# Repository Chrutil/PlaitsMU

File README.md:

# PlaitsMU
The Plaits Macro Oscillator ported to MU

This project is the Plaits Macro Oscillator by Mutable Instruments ported to MU large format modular.

The size of the PCB has been increased and the layout expanded for a 2MU module.
The footprint of most components have been changed to a larger 0805 size, for an easier build.
A few components were left at 0603 size where I could not find a suitable replacement.
The Power connector is a Synthesizers.com standard using -15v/+15v.
There are 12v power regulators added to feed the module the +/-12v it expects.
There is also a footprint for a MOTM power connector, but it is untested. 
I also suspect the io PCB is too wide for a double wide MOTM panel, but I have only tested MU so you are on your own there.

The best way is to select components is to look at the original BOM and pick the appropriate components with the expanded footprint.
I added a file with my parts selection, with no guarantees that I got it correct.

The STM32 mcu is the same as the original module and a very fine pitched IC with 0.5mm pitch so that will be the most challenging part.
I suggest starting with that one to make sure you got that right before populating the rest of the board.

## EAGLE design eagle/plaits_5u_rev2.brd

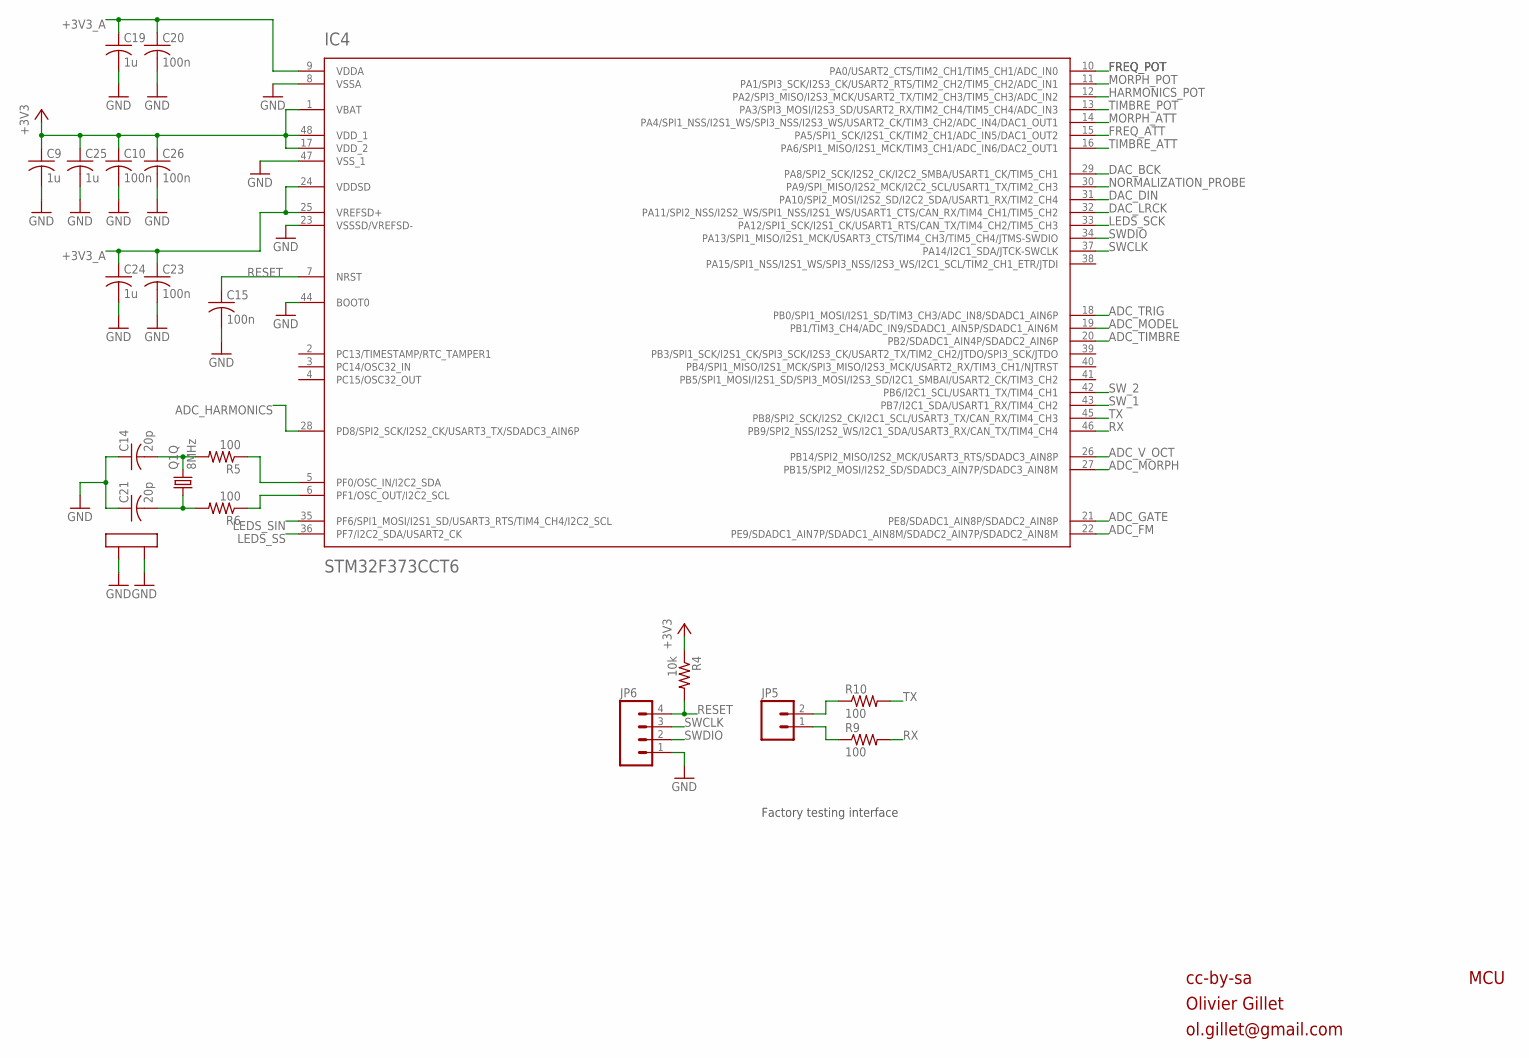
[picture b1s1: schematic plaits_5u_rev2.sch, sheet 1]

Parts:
C9, C19, C24, C25: 1u; C0805
C10, C15, C20, C23, C26: 100n; C0805
C14, C21: 20p; C0805
IC4: STM32F373CCT6; LQFP48
JP5: M02PTH; 1X02
JP6: M04PTH; 1X04
Q1: 8MHz; CTS406
R4: 10k; R0805
R5, R6, R9, R10: 100; R0805

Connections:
+3V3: C9.1, C10.1, C25.1, C26.1, IC4.1 (VBAT), IC4.17 (VDD_2), IC4.48 (VDD_1), R4.1; also elsewhere on the board
+3V3_A: C19.1, C20.1, C23.1, C24.1, IC4.9 (VDDA), IC4.24 (VDDSD), IC4.25 (VREFSD+); also elsewhere on the board
ADC_FM: IC4.22 (PE9/SDADC1_AIN7P/SDADC1_AIN8M/SDADC2_AI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); also elsewhere on the board
ADC_GATE: IC4.21 (PE8/SDADC1_AIN8P/SDADC2_AIN8P); also elsewhere on the board
ADC_HARMONICS: IC4.28 (PD8/SPI2_SCK/I2S2_CK/USART3_TX/SDADC3_A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); also elsewhere on the board
ADC_MODEL: IC4.19 (PB1/TIM3_CH4/ADC_IN9/SDADC1_AIN5P/SDADC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); also elsewhere on the board
ADC_MORPH: IC4.27 (PB15/SPI2_MOSI/I2S2_SD/SDADC3_AIN7P/SDA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); also elsewhere on the board
ADC_TIMBRE: IC4.20 (PB2/SDADC1_AIN4P/SDADC2_AIN6P); also elsewhere on the board
ADC_TRIG: IC4.18 (PB0/SPI1_MOSI/I2S1_SD/TIM3_CH3/ADC_IN8/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); also elsewhere on the board
ADC_V_OCT: IC4.26 (PB14/SPI2_MISO/I2S2_MCK/USART3_RTS/SDAD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); also elsewhere on the board
DAC_BCK: IC4.29 (PA8/SPI2_SCK/I2S2_CK/I2C2_SMBA/USART1_C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); also elsewhere on the board
DAC_DIN: IC4.31 (PA10/SPI2_MOSI/I2S2_SD/I2C2_SDA/USART1_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); also elsewhere on the board
DAC_LRCK: IC4.32 (PA11/SPI2_NSS/I2S2_WS/SPI1_NSS/I2S1_WS/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); also elsewhere on the board
FREQ_ATT: IC4.15 (PA5/SPI1_SCK/I2S1_CK/TIM2_CH1/ADC_IN5/D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); also elsewhere on the board
FREQ_POT: IC4.10 (PA0/USART2_CTS/TIM2_CH1/TIM5_CH1/ADC_IN0); also elsewhere on the board
GND: C9.2, C10.2, C14.1, C15.2, C19.2, C20.2, C21.1, C23.2, C24.2, C25.2, C26.2, IC4.8 (VSSA), IC4.23 (VSSSD/VREFSD-), IC4.44 (BOOT0), IC4.47 (VSS_1), JP6.1, Q1.2 (LID1), Q1.4 (LID2); also elsewhere on the board
HARMONICS_POT: IC4.12 (PA2/SPI3_MISO/I2S3_MCK/USART2_TX/TIM2_C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); also elsewhere on the board
LEDS_SCK: IC4.33 (PA12/SPI1_SCK/I2S1_CK/USART1_RTS/CAN_TX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); also elsewhere on the board
LEDS_SIN: IC4.35 (PF6/SPI1_MOSI/I2S1_SD/USART3_RTS/TIM4_C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); also elsewhere on the board
LEDS_SS: IC4.36 (PF7/I2C2_SDA/USART2_CK); also elsewhere on the board
MORPH_ATT: IC4.14 (PA4/SPI1_NSS/I2S1_WS/SPI3_NSS/I2S3_WS/U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); also elsewhere on the board
MORPH_POT: IC4.11 (PA1/SPI3_SCK/I2S3_CK/USART2_RTS/TIM2_CH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); also elsewhere on the board
unnamed: IC4.5 (PF0/OSC_IN/I2C2_SDA), R5.1
unnamed: IC4.6 (PF1/OSC_OUT/I2C2_SCL), R6.1
unnamed: C14.2, Q1.3 (2), R5.2
unnamed: JP5.2, R10.1
unnamed: C21.2, Q1.1, R6.2
unnamed: JP5.1, R9.1
NORMALIZATION_PROBE: IC4.30 (PA9/SPI_MISO/I2S2_MCK/I2C2_SCL/USART1_T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); also elsewhere on the board
RESET: C15.1, IC4.7 (NRST), JP6.4, R4.2
RX: IC4.46 (PB9/SPI2_NSS/I2S2_WS/I2C1_SDA/USART3_RX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), R9.2
SWCLK: IC4.37 (PA14/I2C1_SDA/JTCK-SWCLK), JP6.3
SWDIO: IC4.34 (PA13/SPI1_MISO/I2S1_MCK/USART3_CTS/TIM4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), JP6.2
SW_1: IC4.43 (PB7/I2C1_SDA/USART1_RX/TIM4_CH2); also elsewhere on the board
SW_2: IC4.42 (PB6/I2C1_SCL/USART1_TX/TIM4_CH1); also elsewhere on the board
TIMBRE_ATT: IC4.16 (PA6/SPI1_MISO/I2S1_MCK/TIM3_CH1/ADC_IN6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); also elsewhere on the board
TIMBRE_POT: IC4.13 (PA3/SPI3_MOSI/I2S3_SD/USART2_RX/TIM2_CH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); also elsewhere on the board
TX: IC4.45 (PB8/SPI2_SCK/I2S2_CK/I2C1_SCL/USART3_TX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), R10.2

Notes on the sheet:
cc-by-sa
Olivier Gillet
ol.gillet@gmail.com
MCU
Factory testing interface

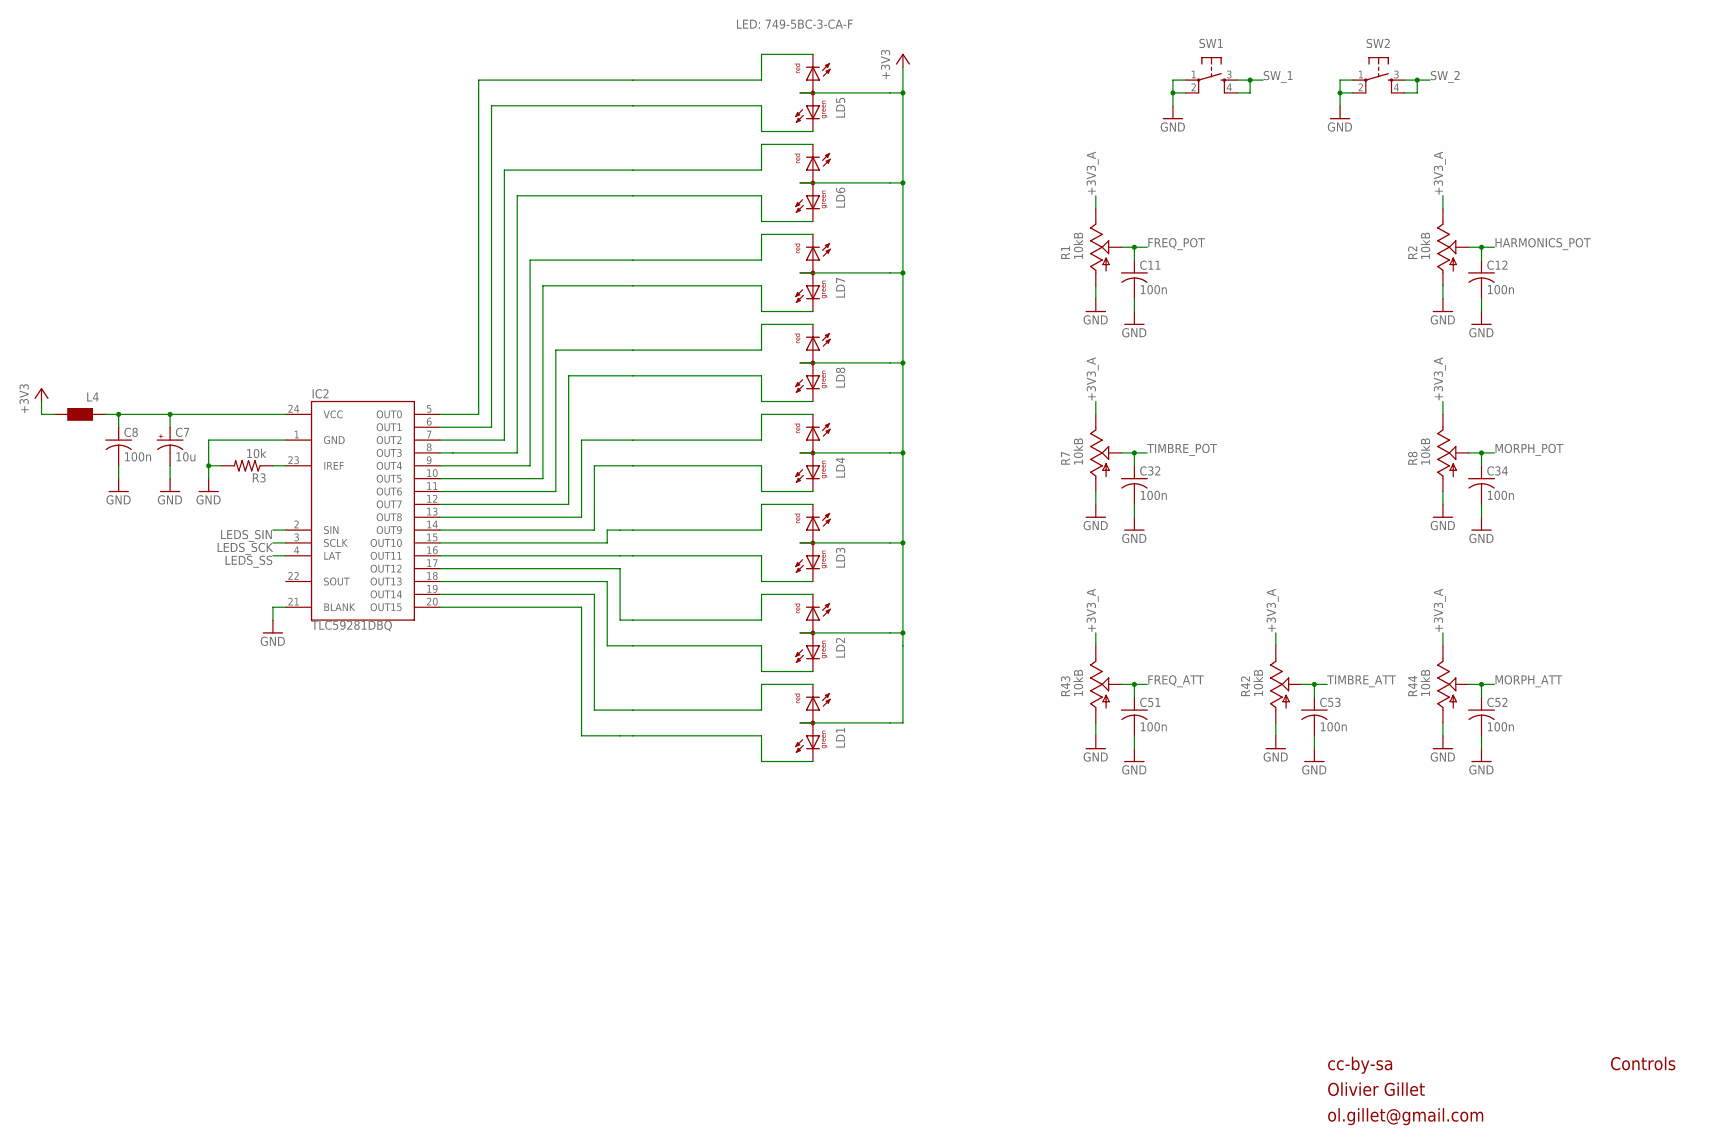
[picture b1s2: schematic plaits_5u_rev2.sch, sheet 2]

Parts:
C7: 10u; PANASONIC_A
C8, C11, C12, C32, C34, C51, C52, C53: 100n; C0805
IC2: TLC59281DBQ; TSSOP24_0635
L4: WE-CBF_0805; 0805
LD1, LD2, LD3, LD4, LD5, LD6, LD7, LD8: DUOLED-RG-A; DUOLED-A-5MM
R1, R2, R7, R8: 10kB; ALPS_POT_VERTICAL_PS
R3: 10k; R0805
R42, R43, R44: 10kB; ALPS_POT_VERTICAL
SW1, SW2: TAC_SWITCHPTH; TACTILE-PTH

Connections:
+3V3: L4.2, LD1.A, LD2.A, LD3.A, LD4.A, LD5.A, LD6.A, LD7.A, LD8.A; also elsewhere on the board
+3V3_A: R1.P$1 (E), R2.P$1 (E), R7.P$1 (E), R8.P$1 (E), R42.P$1 (E), R43.P$1 (E), R44.P$1 (E); also elsewhere on the board
FREQ_ATT: C51.1, R43.P$2 (S); also elsewhere on the board
FREQ_POT: C11.1, R1.P$2 (S); also elsewhere on the board
GND: C7.-, C8.2, C11.2, C12.2, C32.2, C34.2, C51.2, C52.2, C53.2, IC2.1 (GND), IC2.21 (BLANK), R1.P$3 (A), R2.P$3 (A), R3.2, R7.P$3 (A), R8.P$3 (A), R42.P$3 (A), R43.P$3 (A), R44.P$3 (A), SW1.1, SW1.2, SW2.1, SW2.2; also elsewhere on the board
HARMONICS_POT: C12.1, R2.P$2 (S); also elsewhere on the board
LEDS_SCK: IC2.3 (SCLK); also elsewhere on the board
LEDS_SIN: IC2.2 (SIN); also elsewhere on the board
LEDS_SS: IC2.4 (LAT); also elsewhere on the board
MORPH_ATT: C52.1, R44.P$2 (S); also elsewhere on the board
MORPH_POT: C34.1, R8.P$2 (S); also elsewhere on the board
unnamed: IC2.12 (OUT7), LD8.CX (CG)
unnamed: IC2.11 (OUT6), LD8.CR
unnamed: IC2.10 (OUT5), LD7.CX (CG)
unnamed: IC2.9 (OUT4), LD7.CR
unnamed: IC2.8 (OUT3), LD6.CX (CG)
unnamed: IC2.13 (OUT8), LD4.CR
unnamed: IC2.7 (OUT2), LD6.CR
unnamed: IC2.14 (OUT9), LD4.CX (CG)
unnamed: IC2.6 (OUT1), LD5.CX (CG)
unnamed: IC2.15 (OUT10), LD3.CR
unnamed: IC2.16 (OUT11), LD3.CX (CG)
unnamed: IC2.17 (OUT12), LD2.CR
unnamed: IC2.18 (OUT13), LD2.CX (CG)
unnamed: IC2.19 (OUT14), LD1.CR
unnamed: IC2.5 (OUT0), LD5.CR
unnamed: IC2.20 (OUT15), LD1.CX (CG)
unnamed: C7.+, C8.1, IC2.24 (VCC), L4.1
unnamed: IC2.23 (IREF), R3.1
SW_1: SW1.3, SW1.4; also elsewhere on the board
SW_2: SW2.3, SW2.4; also elsewhere on the board
TIMBRE_ATT: C53.1, R42.P$2 (S); also elsewhere on the board
TIMBRE_POT: C32.1, R7.P$2 (S); also elsewhere on the board

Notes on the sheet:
cc-by-sa
Olivier Gillet
ol.gillet@gmail.com
Controls
LED: 749-5BC-3-CA-F

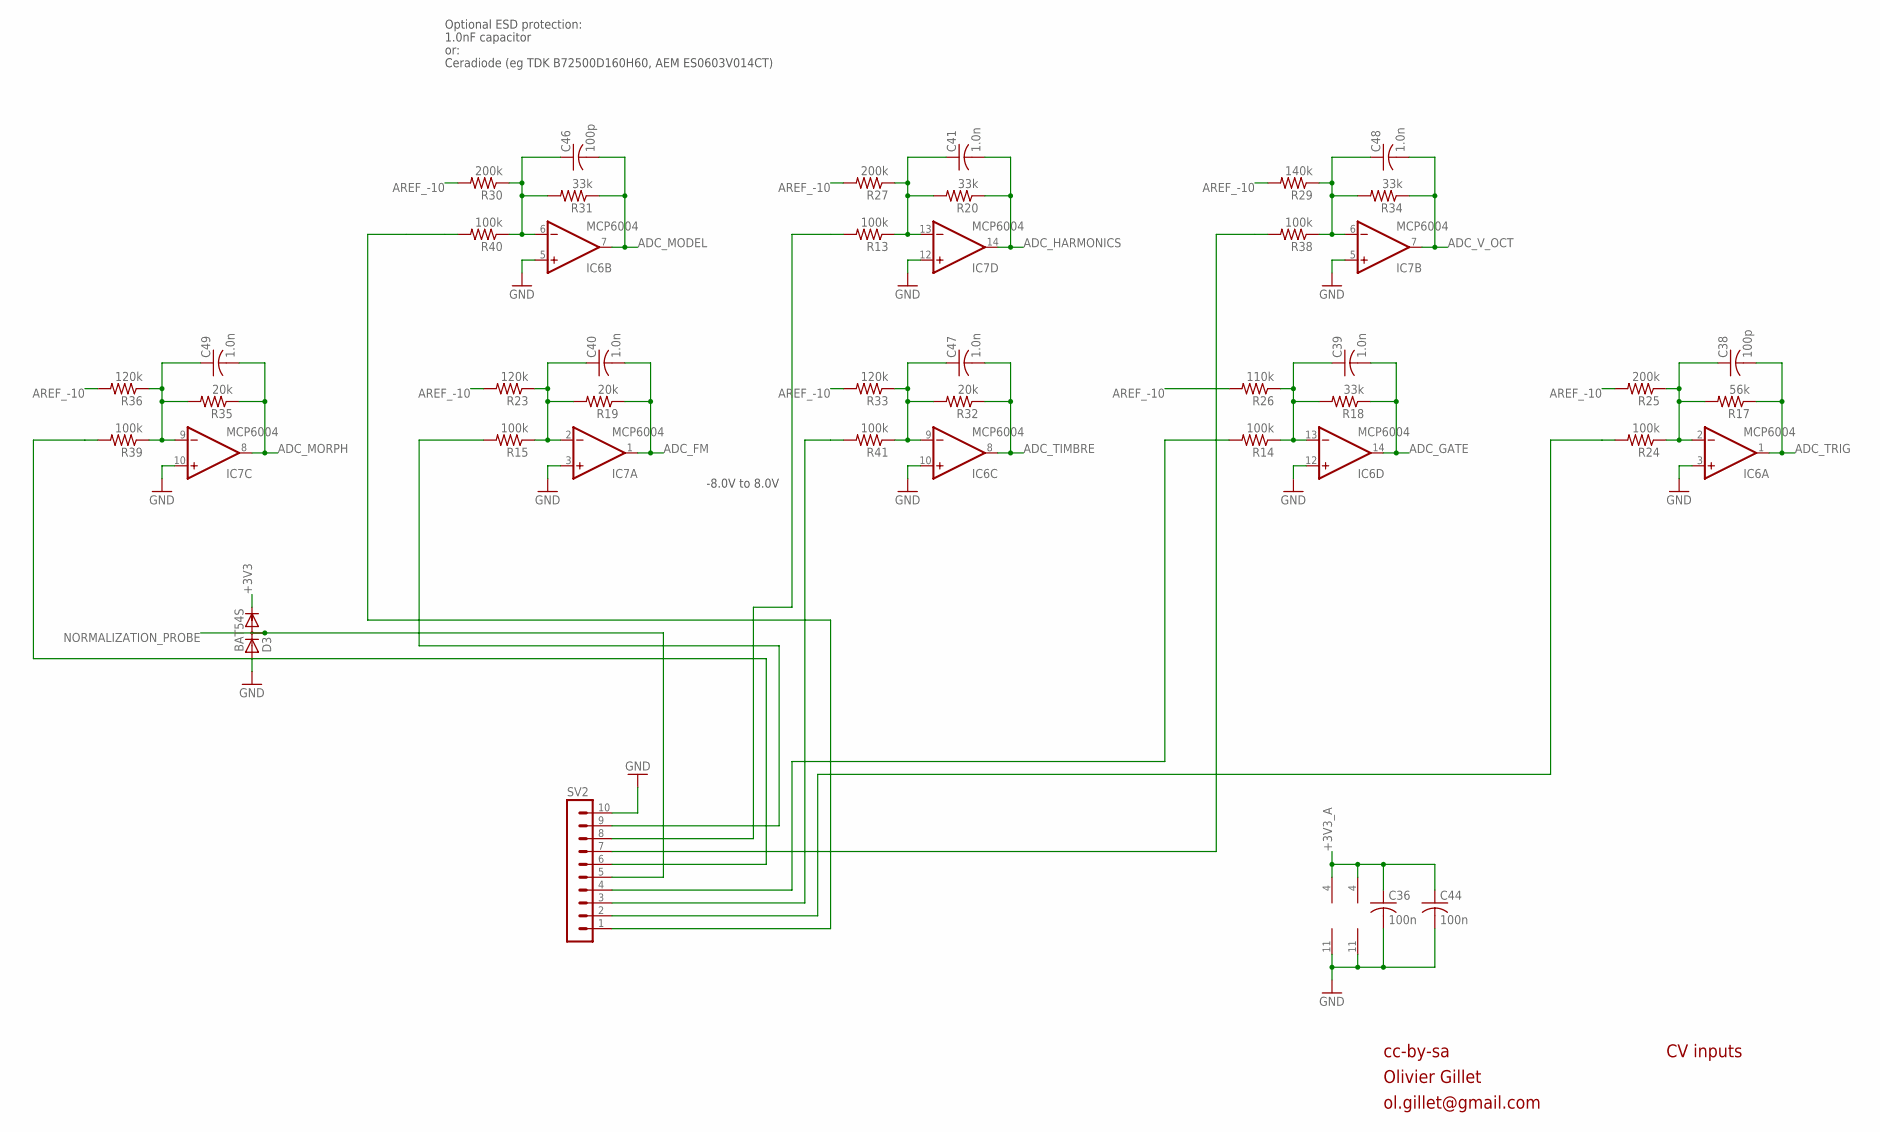
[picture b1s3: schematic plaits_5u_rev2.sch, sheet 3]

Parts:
C36, C44: 100n; C0805
C38, C46: 100p; C0805
C39, C40, C41, C47, C48, C49: 1.0n; C0805
D3: BAT54S; SOT23
IC6, IC7: MCP6004; SO14
R13, R14, R15, R24, R38, R39, R40, R41: 100k; R0805
R17: 56k; R0805
R18, R20, R31, R34: 33k; R0805
R19, R32, R35: 20k; R0805
R23, R33, R36: 120k; R0805
R25, R27, R30: 200k; R0805
R26: 110k; R0805
R29: 140k; R0805
SV2: MA10-1

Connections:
+3V3: D3.2 (C); also elsewhere on the board
+3V3_A: C36.1, C44.1, IC6.4 (V+), IC7.4 (V+); also elsewhere on the board
ADC_FM: C40.2, IC7.1 (OUT), R19.1; also elsewhere on the board
ADC_GATE: C39.2, IC6.14 (OUT), R18.1; also elsewhere on the board
ADC_HARMONICS: C41.2, IC7.14 (OUT), R20.1; also elsewhere on the board
ADC_MODEL: C46.2, IC6.7 (OUT), R31.1; also elsewhere on the board
ADC_MORPH: C49.2, IC7.8 (OUT), R35.1; also elsewhere on the board
ADC_TIMBRE: C47.2, IC6.8 (OUT), R32.1; also elsewhere on the board
ADC_TRIG: C38.2, IC6.1 (OUT), R17.1; also elsewhere on the board
ADC_V_OCT: C48.2, IC7.7 (OUT), R34.1; also elsewhere on the board
AREF_-10: R23.2, R25.2, R26.2, R27.2, R29.2, R30.2, R33.2, R36.2; also elsewhere on the board
FM_IN: R15.2, SV2.9
GATE_IN: R14.2, SV2.4
GATE_IN1: R24.2, SV2.2
GND: C36.2, C44.2, D3.1 (A), IC6.3 (+IN), IC6.5 (+IN), IC6.10 (+IN), IC6.11 (V-), IC6.12 (+IN), IC7.3 (+IN), IC7.5 (+IN), IC7.10 (+IN), IC7.11 (V-), IC7.12 (+IN), SV2.10; also elsewhere on the board
HARMONICS_IN: R13.2, SV2.8
MODEL_IN: R40.2, SV2.1
MORPH_IN: R39.2, SV2.6
unnamed: C38.1, IC6.2 (-IN), R17.2, R24.1, R25.1
unnamed: C39.1, IC6.13 (-IN), R14.1, R18.2, R26.1
unnamed: C48.1, IC7.6 (-IN), R29.1, R34.2, R38.1
unnamed: R41.2, SV2.3
unnamed: C49.1, IC7.9 (-IN), R35.2, R36.1, R39.1
unnamed: C40.1, IC7.2 (-IN), R15.1, R19.2, R23.1
unnamed: C46.1, IC6.6 (-IN), R30.1, R31.2, R40.1
unnamed: C47.1, IC6.9 (-IN), R32.2, R33.1, R41.1
unnamed: C41.1, IC7.13 (-IN), R13.1, R20.2, R27.1
NORMALIZATION_PROBE: D3.3 (AC), SV2.5; also elsewhere on the board
V_OCT_IN: R38.2, SV2.7

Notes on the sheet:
cc-by-sa
Olivier Gillet
ol.gillet@gmail.com
CV inputs
-8.0V to 8.0V
Optional ESD protection:
1.0nF capacitor
or:
Ceradiode (eg TDK B72500D160H60, AEM ES0603V014CT)

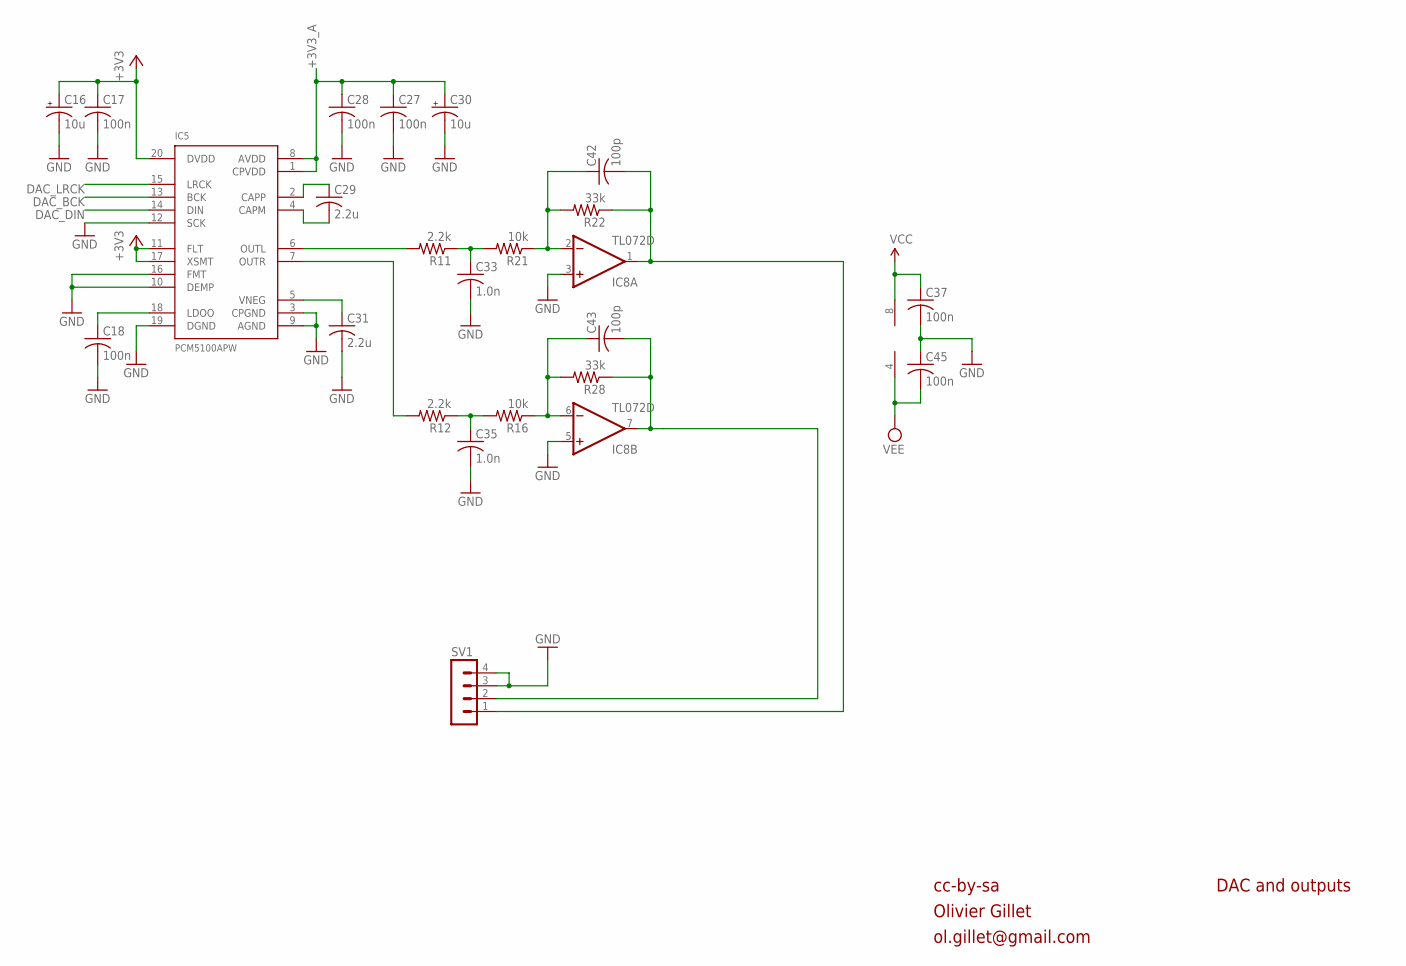
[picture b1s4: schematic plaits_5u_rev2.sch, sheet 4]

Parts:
C16, C30: 10u; PANASONIC_A
C17, C18, C27, C28, C37, C45: 100n; C0805
C29, C31: 2.2u; C0805
C33, C35: 1.0n; C0805
C42, C43: 100p; C0805
IC5: PCM5100APW; SSOP20
IC8: TL072D; SO08
R11, R12: 2.2k; R0805
R16, R21: 10k; R0805
R22, R28: 33k; R0805
SV1: MA04-1

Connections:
+3V3: C16.+, C17.1, IC5.11 (FLT), IC5.17 (XSMT), IC5.20 (DVDD); also elsewhere on the board
+3V3_A: C27.1, C28.1, C30.+, IC5.1 (CPVDD), IC5.8 (AVDD); also elsewhere on the board
DAC_BCK: IC5.13 (BCK); also elsewhere on the board
DAC_DIN: IC5.14 (DIN); also elsewhere on the board
DAC_LRCK: IC5.15 (LRCK); also elsewhere on the board
GND: C16.-, C17.2, C18.2, C27.2, C28.2, C30.-, C31.2, C33.2, C35.2, C37.2, C45.1, IC5.3 (CPGND), IC5.9 (AGND), IC5.10 (DEMP), IC5.12 (SCK), IC5.16 (FMT), IC5.19 (DGND), IC8.3 (+IN), IC8.5 (+IN), SV1.3, SV1.4; also elsewhere on the board
unnamed: C29.1, IC5.2 (CAPP)
unnamed: C29.2, IC5.4 (CAPM)
unnamed: IC5.6 (OUTL), R11.2
unnamed: C33.1, R11.1, R21.2
unnamed: C35.1, R12.1, R16.2
unnamed: C31.1, IC5.5 (VNEG)
unnamed: C18.1, IC5.18 (LDOO)
unnamed: IC5.7 (OUTR), R12.2
unnamed: C43.1, IC8.6 (-IN), R16.1, R28.2
unnamed: C43.2, IC8.7 (OUT), R28.1, SV1.2
unnamed: C42.1, IC8.2 (-IN), R21.1, R22.2
unnamed: C42.2, IC8.1 (OUT), R22.1, SV1.1
VCC: C37.1, IC8.8 (V+); also elsewhere on the board
VEE: C45.2, IC8.4 (V-); also elsewhere on the board

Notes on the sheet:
cc-by-sa
Olivier Gillet
ol.gillet@gmail.com
DAC and outputs

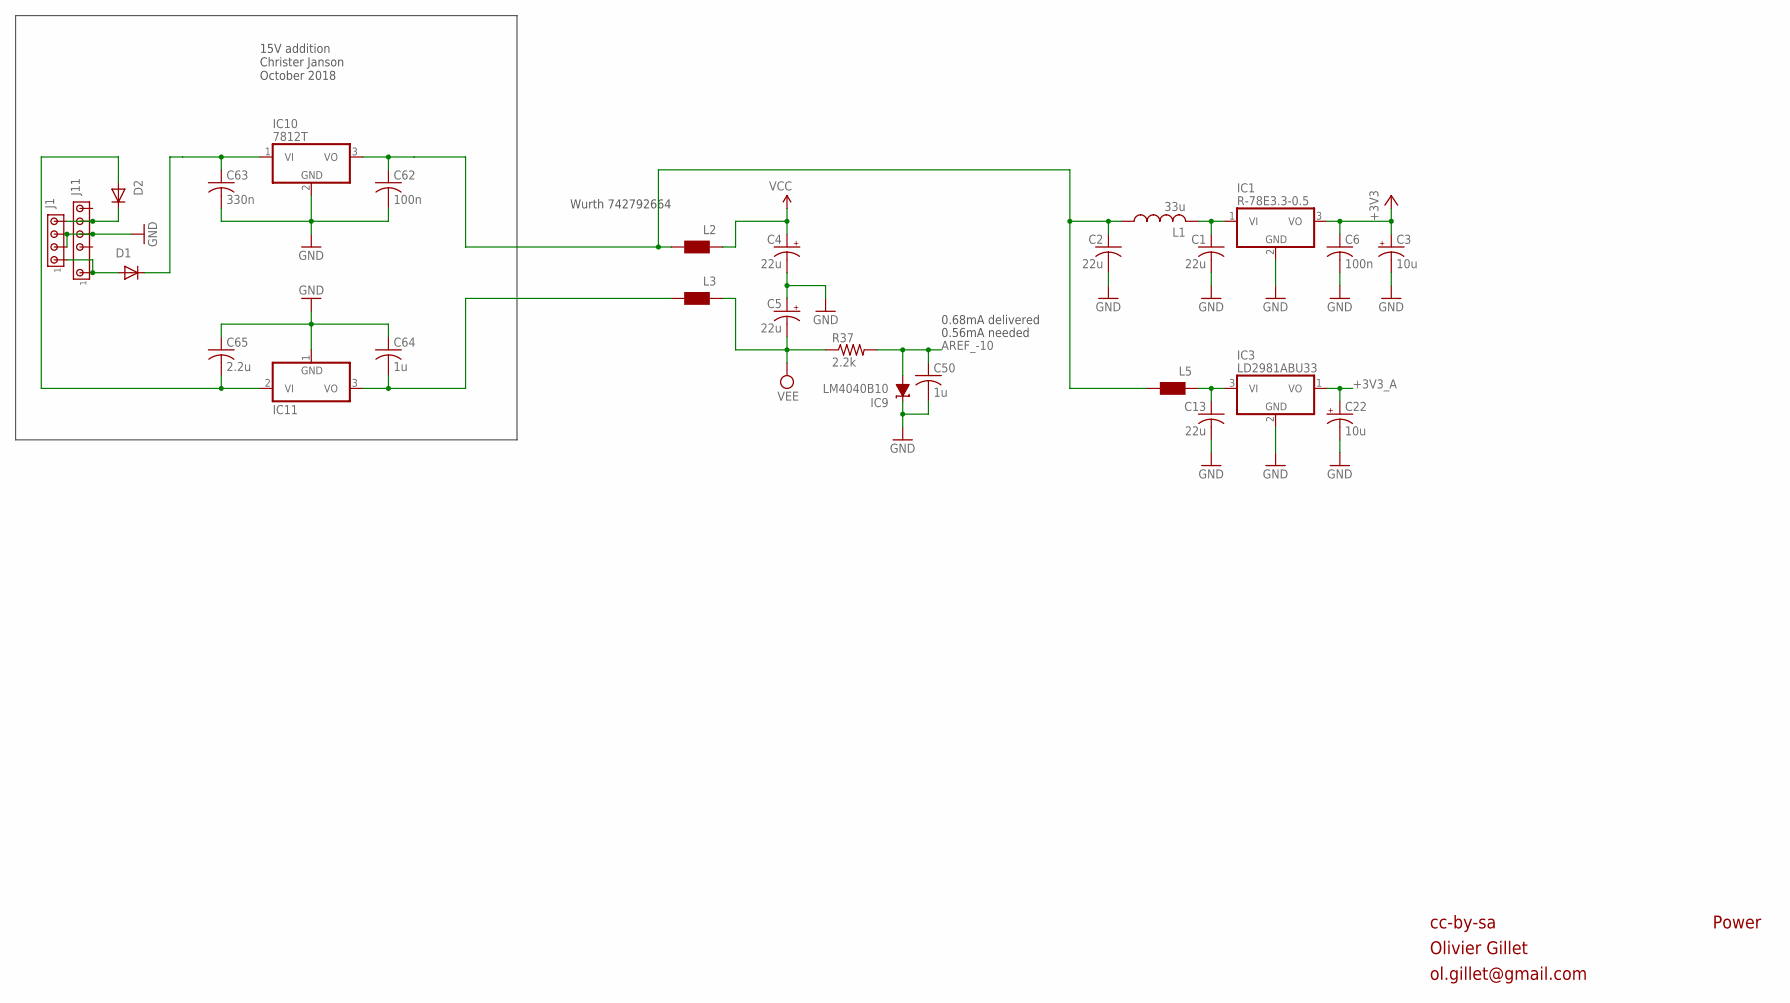
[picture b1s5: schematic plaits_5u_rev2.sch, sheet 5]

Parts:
C1, C2, C13: 22u; C1206
C3, C22: 10u; PANASONIC_A
C4, C5: 22u; PANASONIC_B
C6, C62: 100n; C0805
C50, C64: 1u; C0805
C63: 330n; C0805
C65: 2.2u; C0805
D1, D2: 1N5819HW; SOD123
IC1: R-78E3.3-0.5; WE78
IC3: LD2981ABU33; SOT89
IC9: LM4040B10; DBZ_R-PDSO-G3
IC10: 7812T; TO220H
IC11: 7912T; TO220H
J1: MTA04-156; 1X4MTA
J11: DOTCOMPOWER
L1: 33u; L2012C
L2, L3, L5: WE-CBF_0805; 0805
R37: 2.2k; R0805

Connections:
+3V3: C3.+, C6.1, IC1.3 (VO); also elsewhere on the board
+3V3_A: C22.+, IC3.1 (VO); also elsewhere on the board
AREF_-10: C50.1, IC9.2 (A), R37.2; also elsewhere on the board
GND: C1.2, C2.2, C3.-, C4.-, C5.+, C6.2, C13.2, C22.-, C50.2, C62.2, C63.2, C64.1, C65.1, IC1.2 (GND), IC3.2 (GND), IC9.1 (C), IC10.2 (GND), IC11.1 (GND), J1.2, J1.3, J11.4; also elsewhere on the board
unnamed: C1.1, IC1.1 (VI), L1.2
unnamed: D2.C, J1.4, J11.5
unnamed: C64.2, IC11.3 (VO), L3.2
unnamed: C13.1, IC3.3 (VI), L5.1
unnamed: C2.1, C62.1, IC10.3 (VO), L1.1, L2.2, L5.2
unnamed: C63.1, D1.C, IC10.1 (VI)
unnamed: D1.A, J1.1, J11.1
unnamed: C65.2, D2.A, IC11.2 (VI)
VCC: C4.+, L2.1; also elsewhere on the board
VEE: C5.-, L3.1, R37.1; also elsewhere on the board

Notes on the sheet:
cc-by-sa
Olivier Gillet
ol.gillet@gmail.com
Power
0.56mA needed
Wurth 742792664
0.68mA delivered
15V addition Christer Janson October 2018

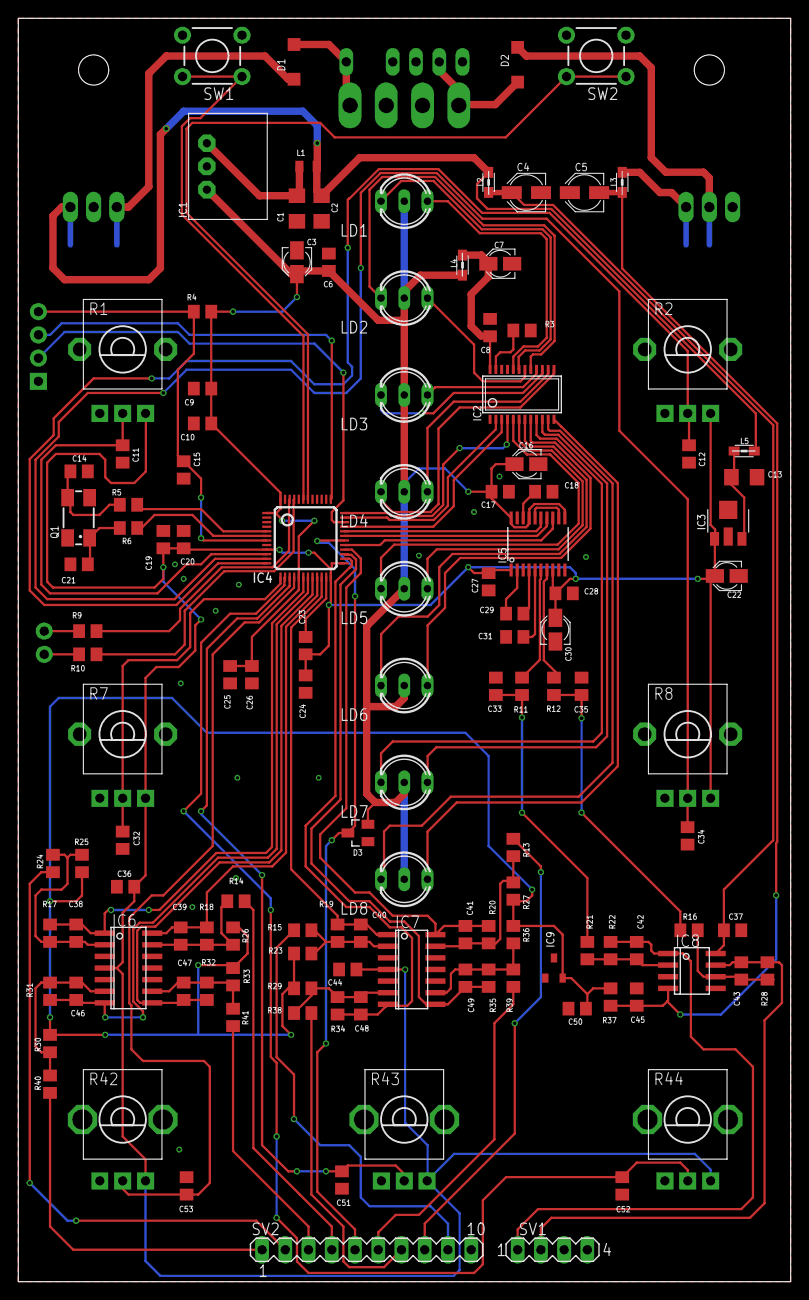
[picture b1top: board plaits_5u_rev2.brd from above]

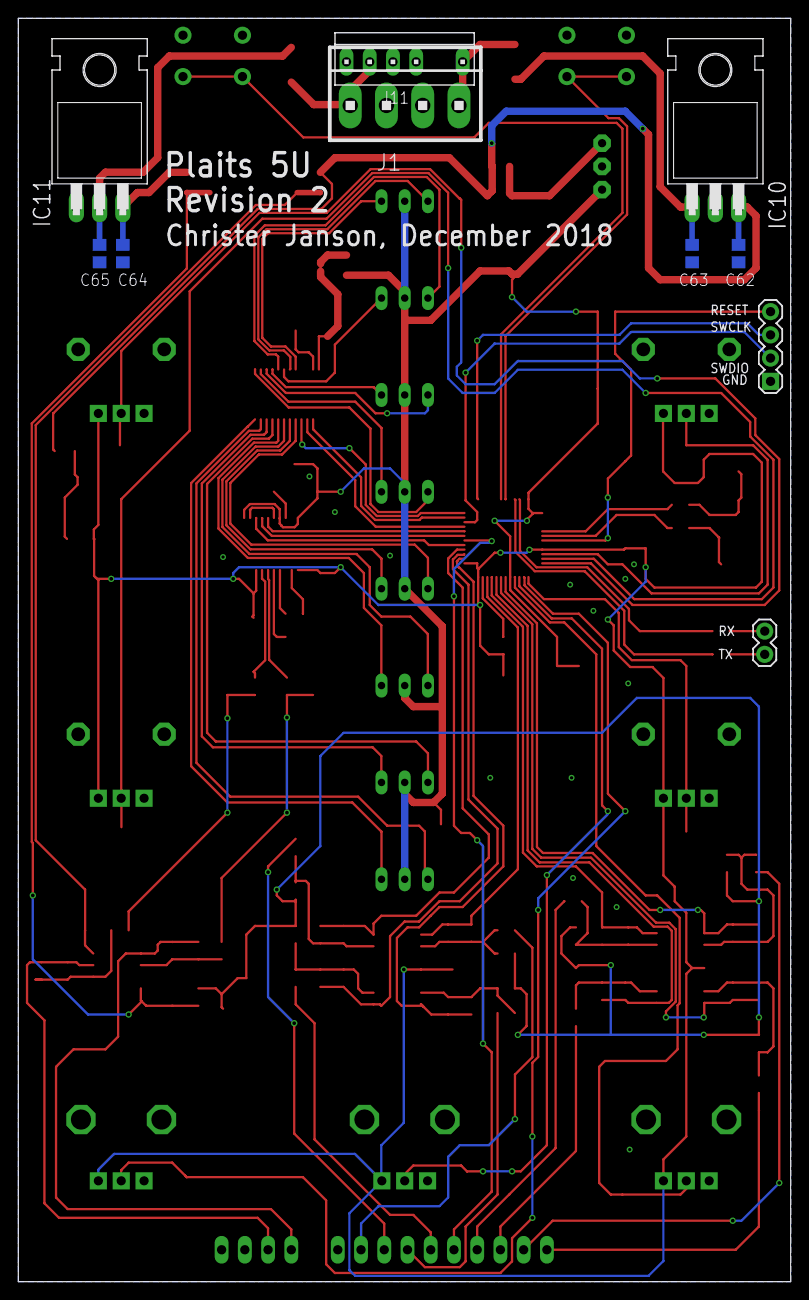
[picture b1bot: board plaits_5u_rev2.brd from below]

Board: 2 copper layers, 84.4 x 138.1 mm, 137 parts (10 on the bottom side), 95 nets.

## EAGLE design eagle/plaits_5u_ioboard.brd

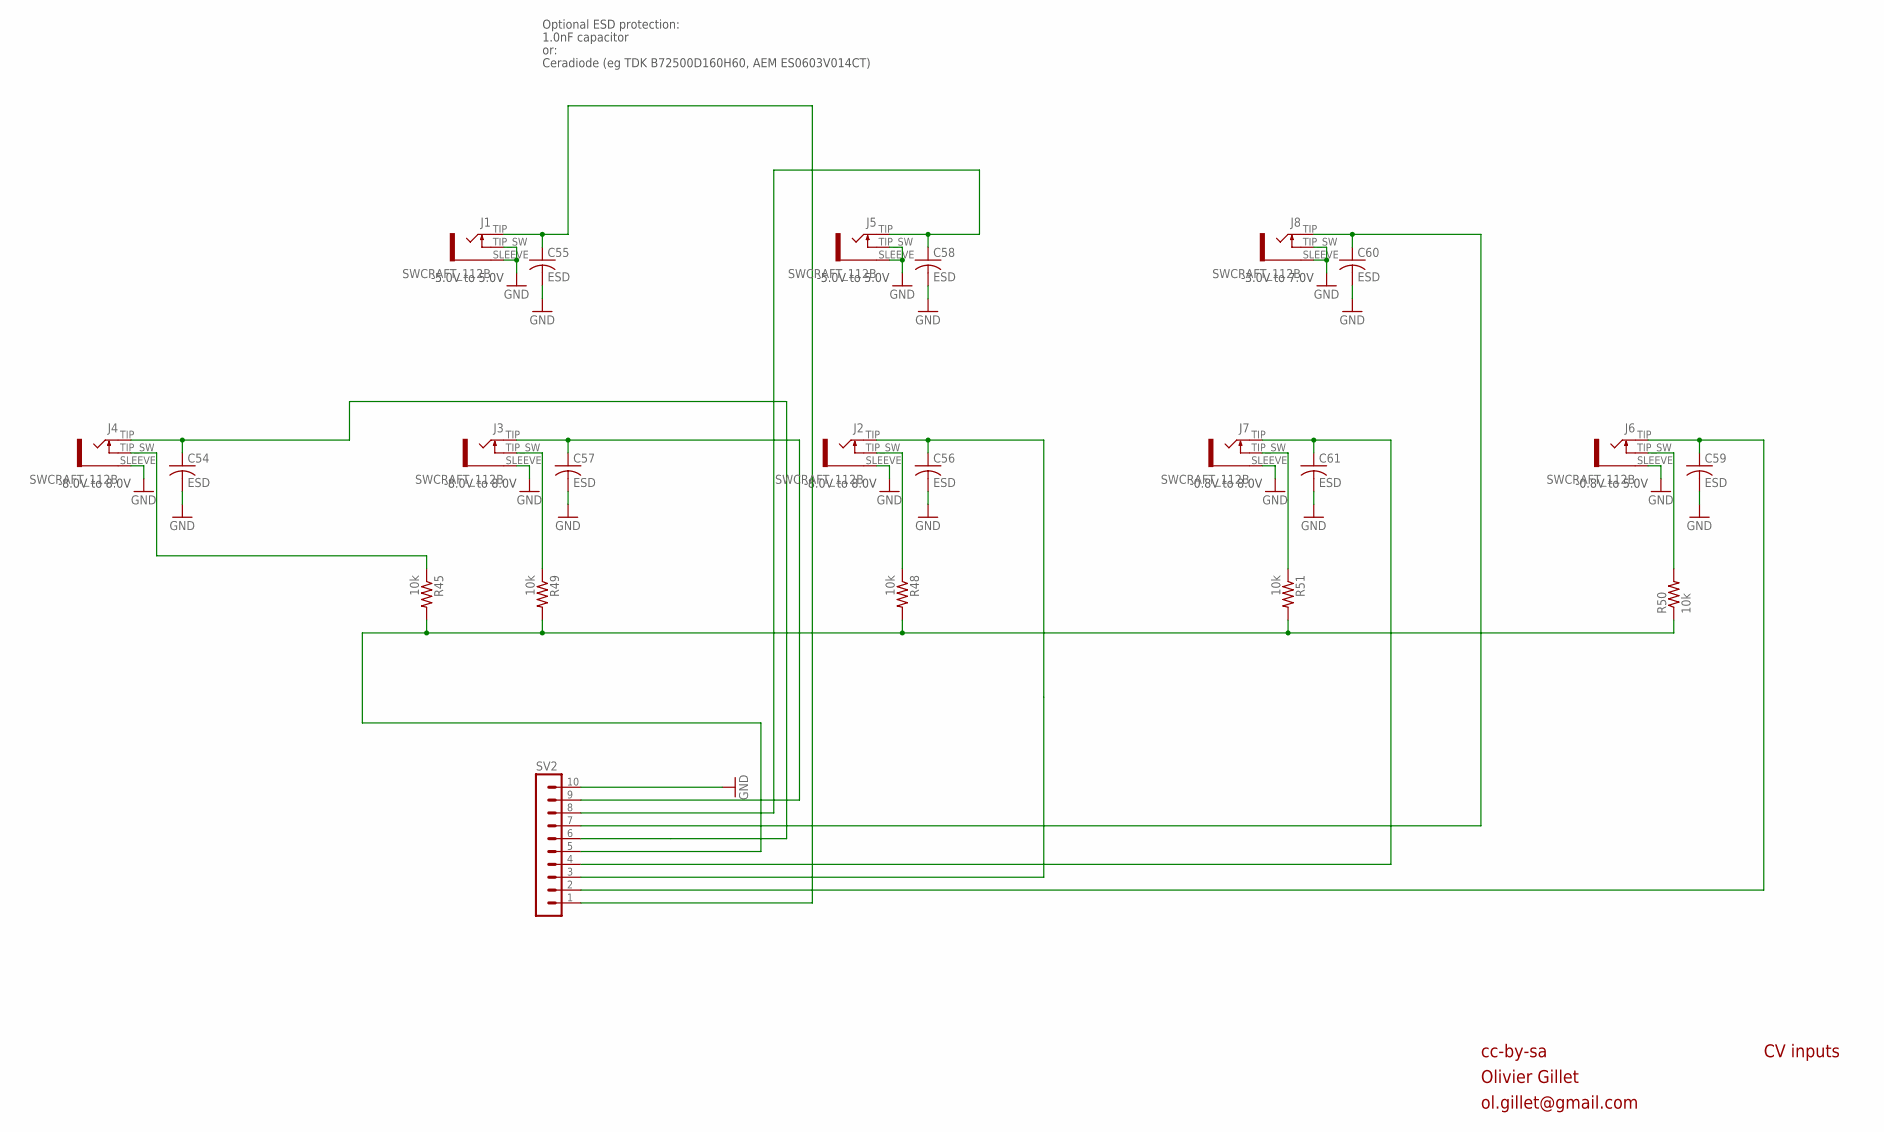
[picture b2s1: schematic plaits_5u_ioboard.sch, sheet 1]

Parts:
C54, C55, C56, C57, C58, C59, C60, C61: ESD; C0805
J1, J2, J3, J4, J5, J6, J7, J8: SWCRAFT_112B; SWCRAFT_112_SLOTS
R45, R48, R49, R50, R51: 10k; R0805
SV2: MA10-1

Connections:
FM_IN: C57.1, J3.TIP (3), SV2.9
GATE_IN: C61.1, J7.TIP (3), SV2.4
GATE_IN1: C59.1, J6.TIP (3), SV2.2
GND: C54.2, C55.2, C56.2, C57.2, C58.2, C59.2, C60.2, C61.2, J1.SLEEVE (5), J1.TIP_SW (4), J2.SLEEVE (5), J3.SLEEVE (5), J4.SLEEVE (5), J5.SLEEVE (5), J5.TIP_SW (4), J6.SLEEVE (5), J7.SLEEVE (5), J8.SLEEVE (5), J8.TIP_SW (4), SV2.10; also elsewhere on the board
HARMONICS_IN: C58.1, J5.TIP (3), SV2.8
MODEL_IN: C55.1, J1.TIP (3), SV2.1
MORPH_IN: C54.1, J4.TIP (3), SV2.6
unnamed: J6.TIP_SW (4), R50.2
unnamed: J3.TIP_SW (4), R49.1
unnamed: J2.TIP_SW (4), R48.1
unnamed: J4.TIP_SW (4), R45.1
unnamed: C56.1, J2.TIP (3), SV2.3
unnamed: J7.TIP_SW (4), R51.1
NORMALIZATION_PROBE: R45.2, R48.2, R49.2, R50.1, R51.2, SV2.5
V_OCT_IN: C60.1, J8.TIP (3), SV2.7

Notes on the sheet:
cc-by-sa
Olivier Gillet
ol.gillet@gmail.com
CV inputs
-3.0V to 7.0V
-8.0V to 8.0V
-5.0V to 5.0V
-0.8V to 8.0V
-0.8V to 5.0V
Optional ESD protection:
1.0nF capacitor
or:
Ceradiode (eg TDK B72500D160H60, AEM ES0603V014CT)

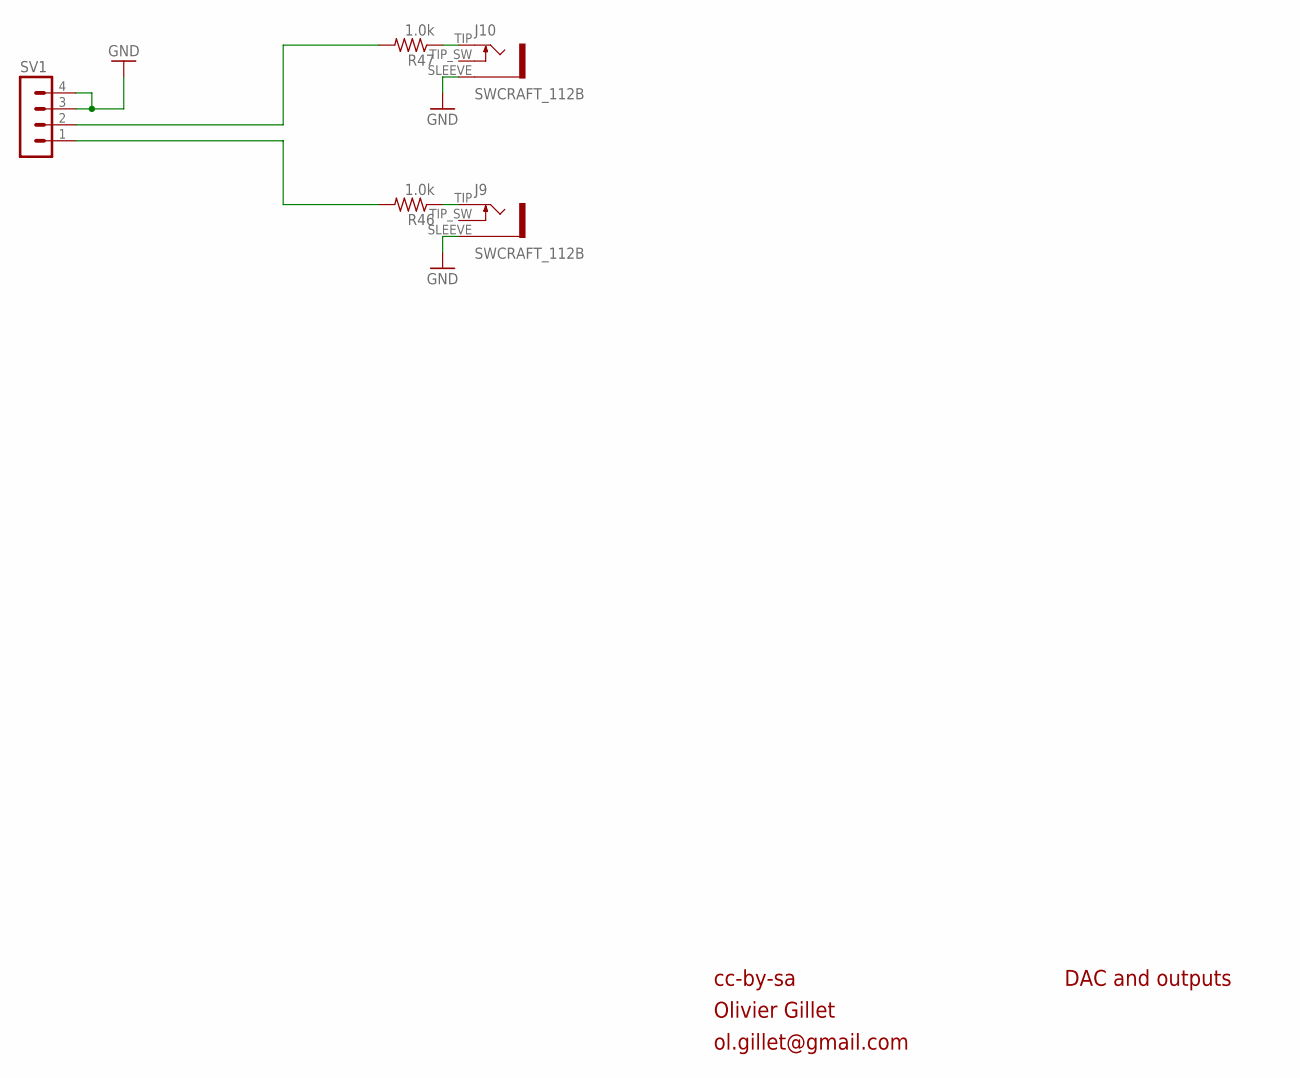
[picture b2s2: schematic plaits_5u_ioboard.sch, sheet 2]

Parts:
J9, J10: SWCRAFT_112B; SWCRAFT_112_SLOTS
R46, R47: 1.0k; R0805
SV1: MA04-1

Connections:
GND: J9.SLEEVE (5), J10.SLEEVE (5), SV1.3, SV1.4; also elsewhere on the board
unnamed: R46.2, SV1.1
unnamed: R47.2, SV1.2
unnamed: J9.TIP (3), R46.1
unnamed: J10.TIP (3), R47.1

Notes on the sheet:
cc-by-sa
Olivier Gillet
ol.gillet@gmail.com
DAC and outputs
